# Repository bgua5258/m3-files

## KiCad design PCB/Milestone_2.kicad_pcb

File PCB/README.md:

### README

**Milestone_2.kicad_sch** shows schematics of the different components in SDR

**Milestone_2.kicad_pcb** puts the components together design in the schematic file to create a PCB with edge mount

The design of the entire PCB consists of a bandpass filter, RF amplifier, Mixer, Audio Amplifier, ADC.
We also included a connector where it will receive the WSPR signal for it to be converted from an analog
signal to a digital one. The bandpass filter will only allow signal with the same frequency of that of a WSPR
signal.}

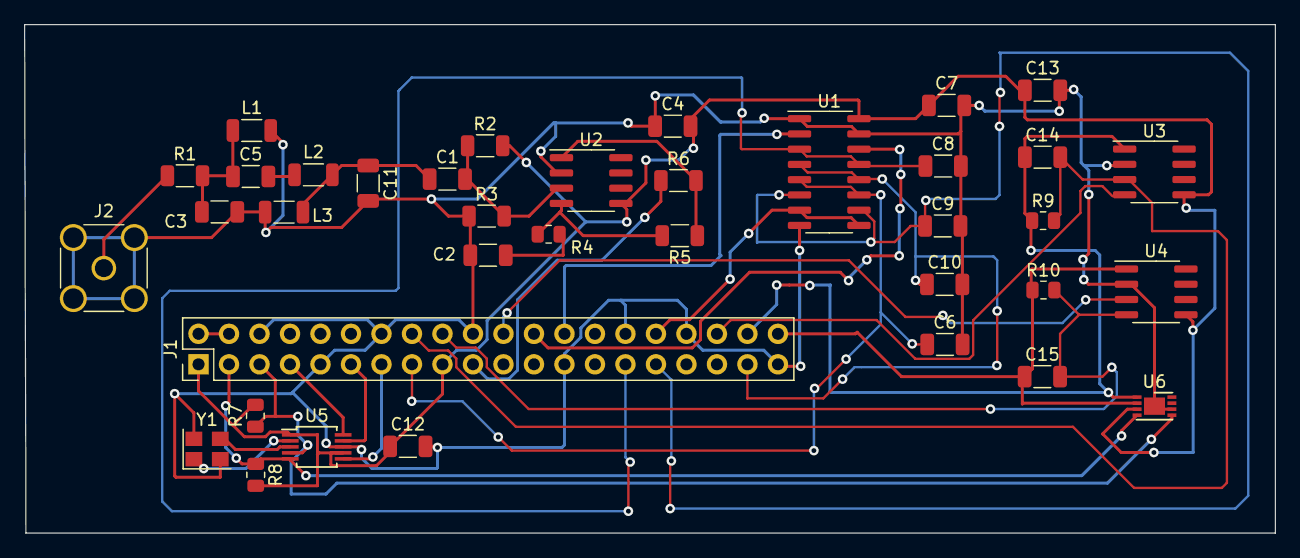
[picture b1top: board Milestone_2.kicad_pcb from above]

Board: 2 copper layers, 104.2 x 42.4 mm, 37 parts (0 on the bottom side), 32 nets.

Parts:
C1: 0.01uF; C_1206_3216Metric
C2, C4, C6, C7, C8, C9, C10, C12, C13: 0.1uF; C_1206_3216Metric
C3, C11: 16.50nF; C_1206_3216Metric
C5: 11.30pF; C_1206_3216Metric
C14, C15: 3300pF; C_1206_3216Metric
J1: Conn_02x20_Odd_Even; PinHeader_2x20_P2.54mm_Vertical
J2: Conn_Coaxial; SMA_Amphenol_132291-12_Vertical
L1, L3: 30.90nH; L_1206_3216Metric
L2: 45.30uH; L_1206_3216Metric
R1: 50; R_1206_3216Metric
R2, R3: 470; R_1206_3216Metric
R4: 47; R_0805_2012Metric
R5: 220; R_1206_3216Metric
R6: 100; R_1206_3216Metric
R7, R8: 4.7k; R_0805_2012Metric
R9, R10: 10K; R_0805_2012Metric
U1: TS3A5017-phwllib; SOIC-16_3.9x9.9mm_P1.27mm
U2: THS4304-phwllib; SOIC-8_3.9x4.9mm_P1.27mm
U3, U4: bbb-rescue_THS4304-phwllib; SOIC-8_3.9x4.9mm_P1.27mm
U5: Si5351A-B-GT; MSOP-10_3x3mm_P0.5mm
U6: MCP3426-xMC; DFN-8-1EP_3x2mm_P0.5mm_EP1.75x1.45mm
Y1: Crystal; Crystal_SMD_TXC_7M-4Pin_3.2x2.5mm

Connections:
+3V3: C4.2, C7.1, C12.1, C13.1, J1.1, J1.17, R2.2, R7.2, R8.2, U1.16 (VCC), U2.5 (V+), U3.5 (V+), U4.5 (V+), U5.1 (VDD), U5.7 (VDDO), U6.3 (VDD)
+5V: J1.2, J1.4
CLK0: J1.7, U5.10 (CLK0)
CLK1: J1.11, U5.9 (CLK1)
CLK2: J1.13, U5.6 (CLK2)
GND: C2.1, C3.2, C4.1, C6.2, C7.2, C8.2, C9.2, C10.2, C11.2, C12.2, C13.2, J1.6, J1.9, J1.14, J1.20, J1.25, J1.30, J1.34, J1.39, J2.2 (Ext), L1.2, L3.1, R3.1, U1.1 (1EN), U1.8 (GND), U1.15 (2EN), U2.2 (V-), U3.2 (V-), U4.2 (V-), U5.8 (GND), U6.6 (VSS), U6.9 (VSS), Y1.2, Y1.4
I2C_SCL: J1.5, R7.1, U5.4 (SCL), U6.5 (SCL)
I2C_SDA: J1.3, R8.1, U5.5 (SDA), U6.4 (SDA)
I+: C14.2, J1.16, R9.2, U3.3 (+)
I-: C15.2, J1.18, R10.2, U4.4 (-)
Iout: C14.1, J1.38, R9.1, U3.1 (VOUT), U6.1 (CH1+)
MIXCLK0: J1.24, U1.14 (IN1)
MIXCLK90: J1.26, U1.2 (IN2)
MIXI+: C6.1, J1.15, U1.5 (1S2), U1.11 (2S2)
MIXI-: C8.1, J1.29, U1.3 (1S4), U1.13 (2S4)
MIXIN: J1.32, U1.7 (1D), U1.9 (2D)
MIXQ+: C9.1, J1.31, U1.6 (1S1), U1.10 (2S1)
MIXQ-: C10.1, J1.37, U1.4 (1S3), U1.12 (2S3)
unnamed: C1.2, R2.1, R3.2, U2.3 (+)
unnamed: C2.2, R4.2
unnamed: C3.1, C5.1, L1.1, R1.2
unnamed: C5.2, L2.1
unnamed: J2.1 (In), R1.1
unnamed: R4.1, R5.2, U2.4 (-)
unnamed: R5.1, R6.2, U2.1 (VOUT)
unnamed: U5.2 (XA), Y1.1
unnamed: U5.3 (XB), Y1.3
Q+: J1.22, U4.3 (+)
Q-: J1.36, U3.4 (-)
Qout: C15.1, J1.40, R10.1, U4.1 (VOUT), U6.2 (CH1-)
RFIN: C1.1, C11.1, L2.2, L3.2
RFOUT: J1.19, R6.1

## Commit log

2022-06-02 asdasd
    asdasd
